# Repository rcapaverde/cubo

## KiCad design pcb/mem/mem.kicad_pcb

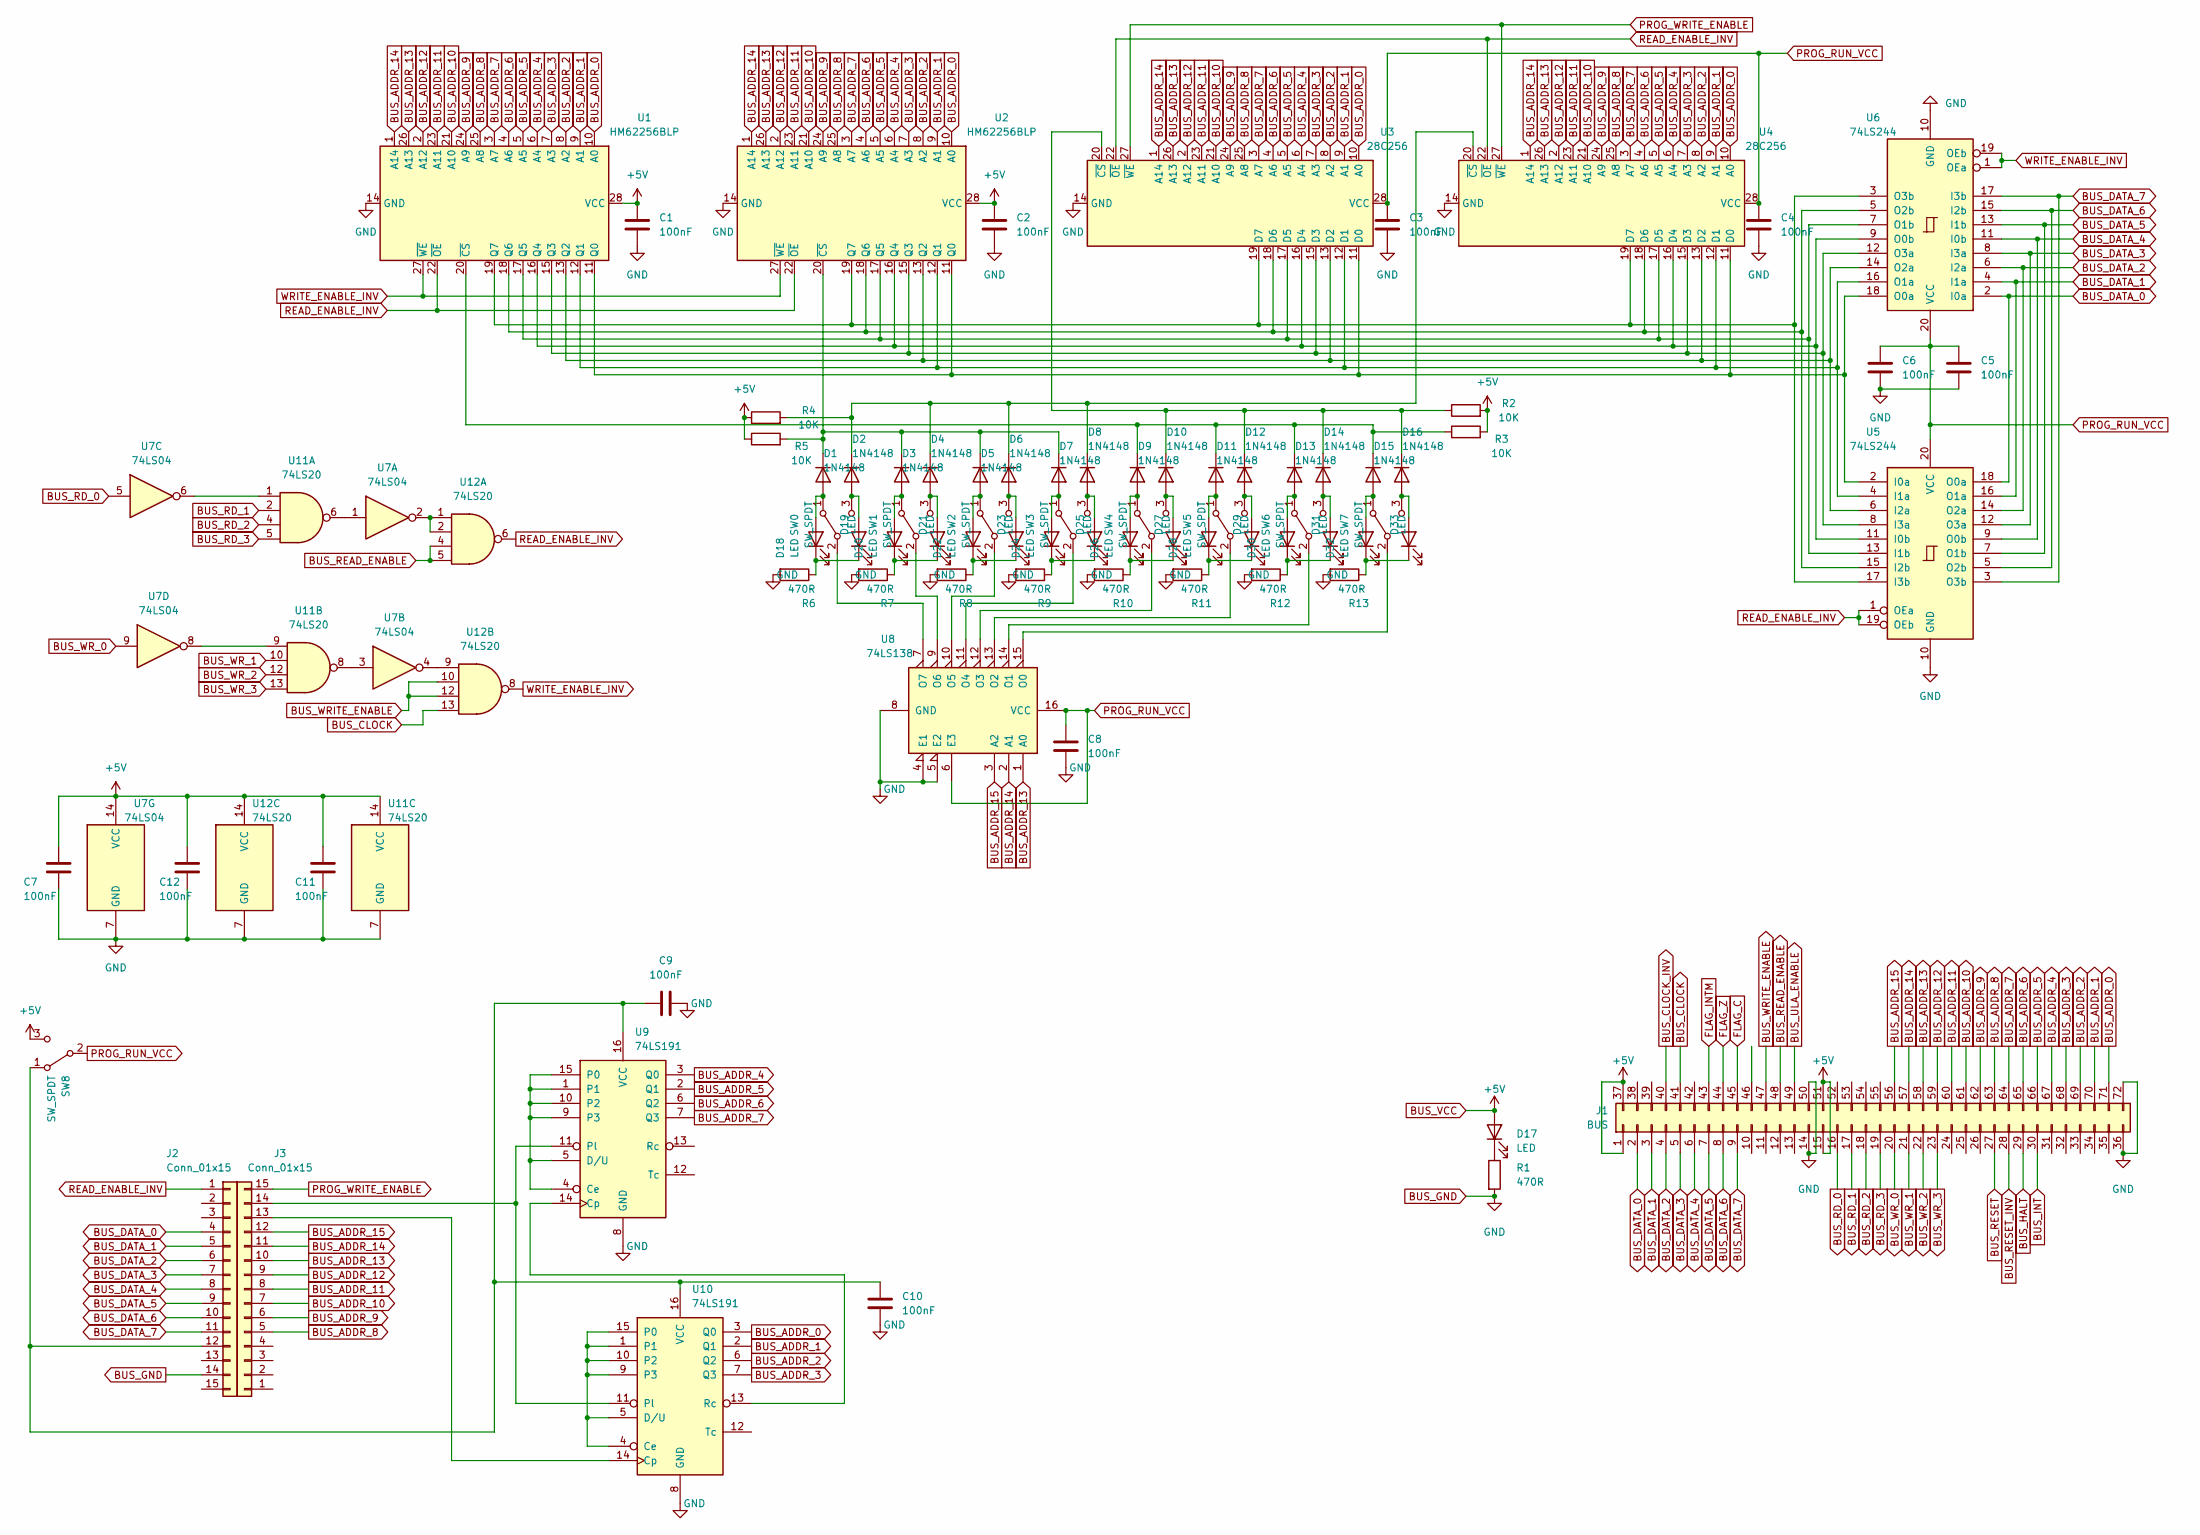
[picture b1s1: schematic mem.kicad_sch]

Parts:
C1, C2, C3, C4, C5, C6, C7, C8, C9, C10, C11, C12: 100nF; C_Disc_D4.3mm_W1.9mm_P5.00mm
D1, D2, D3, D4, D5, D6, D7, D8, D9, D10, D11, D12, D13, D14, D15, D16: 1N4148; D_DO-35_SOD27_P7.62mm_Horizontal
D17, D18, D19, D20, D21, D22, D23, D24, D25, D26, D27, D28, D29, D30, D31, D32, D33: LED; LED_D5.0mm
J1: BUS; Card Edge Slot 28+44
J2, J3: Conn_01x15; PinHeader_1x15_P2.54mm_Vertical
R1, R6, R7, R8, R9, R10, R11, R12, R13: 470R; R_Axial_DIN0204_L3.6mm_D1.6mm_P7.62mm_Horizontal
R2, R3, R4, R5: 10K; R_Axial_DIN0204_L3.6mm_D1.6mm_P7.62mm_Horizontal
SW0, SW1, SW2, SW3, SW4, SW5, SW6, SW7, SW8: SW_SPDT; PinHeader_1x03_P2.54mm_Vertical
U1, U2: HM62256BLP; DIP-28_W15.24mm
U3, U4: 28C256; DIP-28_W15.24mm_Socket
U5, U6: 74LS244; DIP-20_W7.62mm_Socket
U7: 74LS04; DIP-14_W7.62mm_Socket
U8: 74LS138; DIP-16_W7.62mm_Socket
U9, U10: 74LS191; DIP-16_W7.62mm_Socket
U11, U12: 74LS20; DIP-14_W7.62mm_Socket

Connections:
BUS_ADDR_0: J1.71, U1.10 (A0), U2.10 (A0), U3.10 (A0), U4.10 (A0), U10.3 (Q0)
BUS_ADDR_1: J1.70, U1.9 (A1), U2.9 (A1), U3.9 (A1), U4.9 (A1), U10.2 (Q1)
BUS_ADDR_2: J1.69, U1.8 (A2), U2.8 (A2), U3.8 (A2), U4.8 (A2), U10.6 (Q2)
BUS_ADDR_3: J1.68, U1.7 (A3), U2.7 (A3), U3.7 (A3), U4.7 (A3), U10.7 (Q3)
BUS_ADDR_4: J1.67, U1.6 (A4), U2.6 (A4), U3.6 (A4), U4.6 (A4), U9.3 (Q0)
BUS_ADDR_5: J1.66, U1.5 (A5), U2.5 (A5), U3.5 (A5), U4.5 (A5), U9.2 (Q1)
BUS_ADDR_6: J1.65, U1.4 (A6), U2.4 (A6), U3.4 (A6), U4.4 (A6), U9.6 (Q2)
BUS_ADDR_7: J1.64, U1.3 (A7), U2.3 (A7), U3.3 (A7), U4.3 (A7), U9.7 (Q3)
BUS_ADDR_8: J1.63, J3.5, U1.25 (A8), U2.25 (A8), U3.25 (A8), U4.25 (A8)
BUS_ADDR_9: J1.62, J3.6, U1.24 (A9), U2.24 (A9), U3.24 (A9), U4.24 (A9)
BUS_ADDR_10: J1.61, J3.7, U1.21 (A10), U2.21 (A10), U3.21 (A10), U4.21 (A10)
BUS_ADDR_11: J1.60, J3.8, U1.23 (A11), U2.23 (A11), U3.23 (A11), U4.23 (A11)
BUS_ADDR_12: J1.59, J3.9, U1.2 (A12), U2.2 (A12), U3.2 (A12), U4.2 (A12)
BUS_ADDR_13: J1.58, J3.10, U1.26 (A13), U2.26 (A13), U3.26 (A13), U4.26 (A13), U8.1 (A0)
BUS_ADDR_14: J1.57, J3.11, U1.1 (A14), U2.1 (A14), U3.1 (A14), U4.1 (A14), U8.2 (A1)
BUS_ADDR_15: J1.56, J3.12, U8.3 (A2)
BUS_CLOCK: J1.41, U12.13
BUS_CLOCK_INV: J1.40
BUS_DATA_0: J1.2, J2.4, U5.18 (O0a), U6.2 (I0a)
BUS_DATA_1: J1.3, J2.5, U5.16 (O1a), U6.4 (I1a)
BUS_DATA_2: J1.4, J2.6, U5.14 (O2a), U6.6 (I2a)
BUS_DATA_3: J1.5, J2.7, U5.12 (O3a), U6.8 (I3a)
BUS_DATA_4: J1.6, J2.8, U5.9 (O0b), U6.11 (I0b)
BUS_DATA_5: J1.7, J2.9, U5.7 (O1b), U6.13 (I1b)
BUS_DATA_6: J1.8, J2.10, U5.5 (O2b), U6.15 (I2b)
BUS_DATA_7: J1.9, J2.11, U5.3 (O3b), U6.17 (I3b)
BUS_GND: C1.2, C2.2, C3.2, C4.2, C5.2, C6.2, C7.2, C8.2, C9.2, C10.2, C11.2, C12.2, J1.14, J1.36, J1.50, J1.72, J2.14, R1.2, R6.2, R7.2, R8.2, R9.2, R10.2, R11.2, R12.2, R13.2, U1.14 (GND), U2.14 (GND), U3.14 (GND), U4.14 (GND), U5.10 (GND), U6.10 (GND), U7.7 (GND), U8.4 (E1), U8.5 (E2), U8.8 (GND), U9.8 (GND), U10.8 (GND), U11.7 (GND), U12.7 (GND); also elsewhere on the board
BUS_HALT: J1.29
BUS_INT: J1.30
BUS_RD_0: J1.16, U7.5
BUS_RD_1: J1.17, U11.2
BUS_RD_2: J1.18, U11.4
BUS_RD_3: J1.19, U11.5
BUS_RESET: J1.27
BUS_RESET_INV: J1.28
BUS_ULA_ENABLE: J1.49
BUS_VCC: C1.1, C2.1, C7.1, C11.1, C12.1, D17.2 (A), J1.1, J1.15, J1.37, J1.51, R2.2, R3.2, R4.1, R5.1, SW8.3 (C), U1.28 (VCC), U2.28 (VCC), U7.14 (VCC), U11.14 (VCC), U12.14 (VCC)
BUS_WR_0: J1.20, U7.9
BUS_WR_1: J1.21, U11.10
BUS_WR_2: J1.22, U11.12
BUS_WR_3: J1.23, U11.13
FLAG_C: J1.45
FLAG_INTM: J1.43
FLAG_Z: J1.44
unnamed: D1.1 (K), D3.1 (K), D5.1 (K), D7.1 (K), R5.2, U2.20 (~CS)
unnamed: D2.1 (K), D4.1 (K), D6.1 (K), D8.1 (K), R4.2, U4.20 (~CS)
unnamed: D3.2 (A), D20.2 (A), SW1.1 (A)
unnamed: D4.2 (A), D21.2 (A), SW1.3 (C)
unnamed: D5.2 (A), D22.2 (A), SW2.1 (A)
unnamed: D6.2 (A), D23.2 (A), SW2.3 (C)
unnamed: D7.2 (A), D24.2 (A), SW3.1 (A)
unnamed: D8.2 (A), D25.2 (A), SW3.3 (C)
unnamed: D9.2 (A), D26.2 (A), SW4.1 (A)
unnamed: D10.1 (K), D12.1 (K), D14.1 (K), D16.1 (K), R2.1, U3.20 (~CS)
unnamed: D10.2 (A), D27.2 (A), SW4.3 (C)
unnamed: D9.1 (K), D11.1 (K), D13.1 (K), D15.1 (K), R3.1, U1.20 (~CS)
unnamed: D11.2 (A), D28.2 (A), SW5.1 (A)
unnamed: D12.2 (A), D29.2 (A), SW5.3 (C)
unnamed: D13.2 (A), D30.2 (A), SW6.1 (A)
unnamed: D14.2 (A), D31.2 (A), SW6.3 (C)
unnamed: D15.2 (A), D32.2 (A), SW7.1 (A)
unnamed: D16.2 (A), D33.2 (A), SW7.3 (C)
unnamed: D17.1 (K), R1.1
unnamed 63: D18.1 (K), D19.1 (K), R6.1; also elsewhere on the board
unnamed: D20.1 (K), D21.1 (K), R7.1
unnamed: D22.1 (K), D23.1 (K), R8.1
unnamed: D24.1 (K), D25.1 (K), R9.1
unnamed: D26.1 (K), D27.1 (K), R10.1
unnamed: D28.1 (K), D29.1 (K), R11.1
unnamed: D30.1 (K), D31.1 (K), R12.1
unnamed: D32.1 (K), D33.1 (K), R13.1
unnamed: SW0.2 (B), U8.7 (O7)
unnamed: SW1.2 (B), U8.9 (O6)
unnamed: SW2.2 (B), U8.10 (O5)
unnamed: SW3.2 (B), U8.11 (O4)
unnamed: SW4.2 (B), U8.12 (O3)
unnamed: SW5.2 (B), U8.13 (O2)
unnamed: SW6.2 (B), U8.14 (O1)
unnamed: SW7.2 (B), U8.15 (O0)
unnamed: C9.1, C10.1, J2.12, SW8.1 (A), U9.16 (VCC), U10.16 (VCC)
unnamed: U1.11 (Q0), U2.11 (Q0), U3.11 (D0), U4.11 (D0), U5.2 (I0a), U6.18 (O0a)
unnamed: U1.12 (Q1), U2.12 (Q1), U3.12 (D1), U4.12 (D1), U5.4 (I1a), U6.16 (O1a)
unnamed: U1.13 (Q2), U2.13 (Q2), U3.13 (D2), U4.13 (D2), U5.6 (I2a), U6.14 (O2a)
unnamed: U1.15 (Q3), U2.15 (Q3), U3.15 (D3), U4.15 (D3), U5.8 (I3a), U6.12 (O3a)
unnamed: U1.16 (Q4), U2.16 (Q4), U3.16 (D4), U4.16 (D4), U5.11 (I0b), U6.9 (O0b)
unnamed: U1.17 (Q5), U2.17 (Q5), U3.17 (D5), U4.17 (D5), U5.13 (I1b), U6.7 (O1b)
unnamed: U1.18 (Q6), U2.18 (Q6), U3.18 (D6), U4.18 (D6), U5.15 (I2b), U6.5 (O2b)
unnamed: U1.19 (Q7), U2.19 (Q7), U3.19 (D7), U4.19 (D7), U5.17 (I3b), U6.3 (O3b)
unnamed: U7.2, U12.1, U12.2
unnamed: U7.4, U12.9
unnamed: U7.6, U11.1
unnamed: U9.1, U9.4 (Ce), U9.5 (D/U), U9.9 (P3), U9.10 (P2), U9.15 (P0)
unnamed: J3.14, U9.11 (Pl), U10.11 (Pl)
unnamed: U9.14 (Cp), U10.13 (Rc)
unnamed: J3.13, U10.14 (Cp)
unnamed: U10.1, U10.4 (Ce), U10.5 (D/U), U10.9 (P3), U10.10 (P2), U10.15 (P0)
unnamed: U7.1, U11.6
unnamed: U7.3, U11.8
unnamed: U7.8, U11.9
PROG_RUN_VCC: C3.1, C4.1, C5.1, C6.1, C8.1, SW8.2 (B), U3.28 (VCC), U4.28 (VCC), U5.20 (VCC), U6.20 (VCC), U8.6 (E3), U8.16 (VCC)
PROG_WRITE_ENABLE: J3.15, U3.27 (~WE), U4.27 (~WE)
READ_ENABLE_INV: J2.1, U1.22 (~OE), U2.22 (~OE), U3.22 (~OE), U4.22 (~OE), U5.1 (OEa), U5.19 (OEb), U12.6
WRITE_ENABLE_INV: U1.27 (~WE), U2.27 (~WE), U6.1 (OEa), U6.19 (OEb), U12.8

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
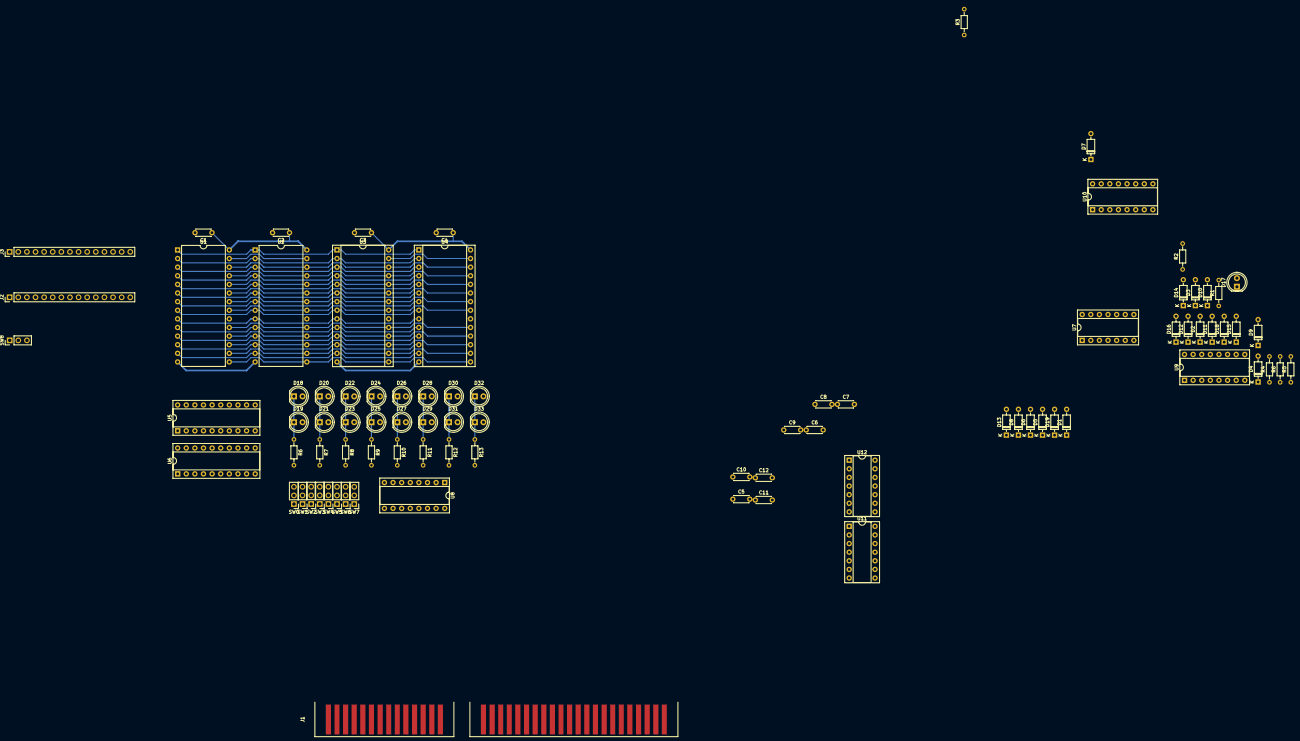
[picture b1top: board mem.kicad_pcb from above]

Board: 2 copper layers, 85 parts (0 on the bottom side), 98 nets.

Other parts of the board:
D18#2, D19#2: LED; LED_D5.0mm
R6#2: 10K; R_Axial_DIN0204_L3.6mm_D1.6mm_P7.62mm_Horizontal

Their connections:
BUS_GND: R6#2.1; also elsewhere on the board
unnamed 63: D18#2.1 (K), D19#2.1 (K), R6#2.2; also elsewhere on the board

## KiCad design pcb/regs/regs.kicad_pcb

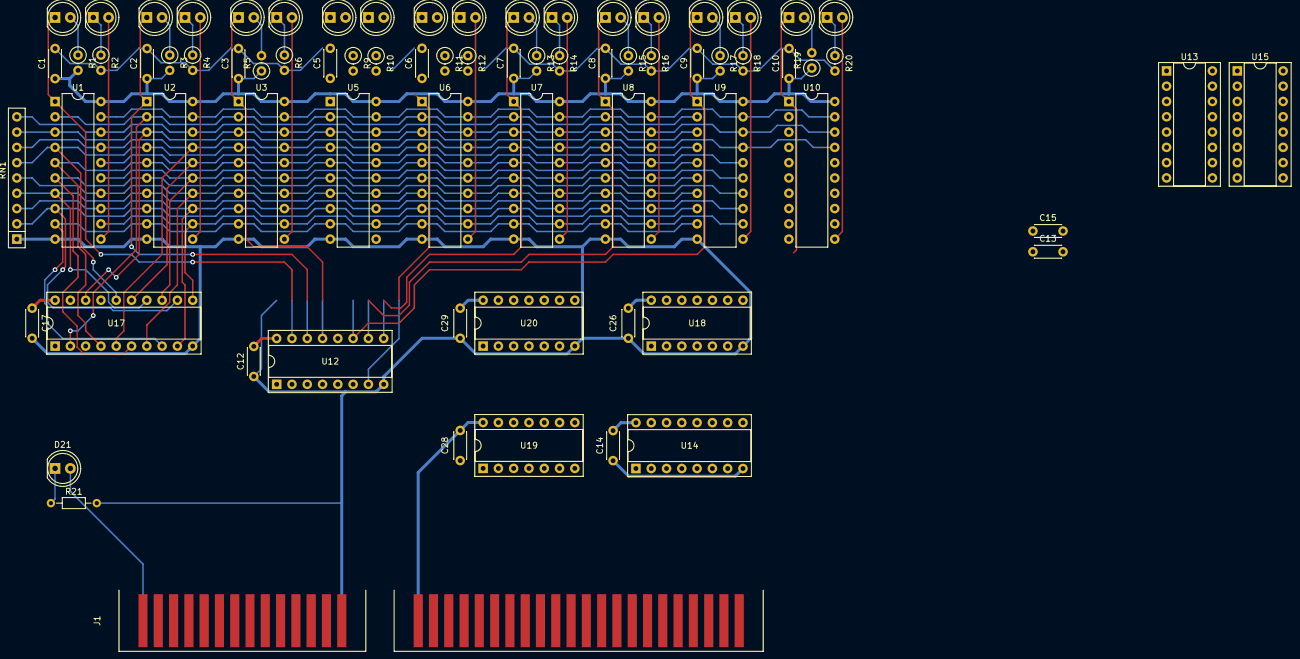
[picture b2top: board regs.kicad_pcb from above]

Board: 2 copper layers, 74 parts (0 on the bottom side), 78 nets.

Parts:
C1, C2, C3, C5, C6, C7, C8, C9, C10, C12, C13, C14, C15, C17, C26, C28, C29: 100nF; C_Disc_D4.3mm_W1.9mm_P5.00mm
D1, D2, D3, D4, D5, D6, D9, D10, D11, D12, D13, D14, D15, D16, D17, D18, D19, D20, D21: LED; LED_D5.0mm
J1: BUS; Card Edge Slot 28+44
R1, R2, R3, R4, R5, R6, R9, R10, R11, R12, R13, R14, R15, R16, R17, R18, R19, R20: 470R; R_Axial_DIN0207_L6.3mm_D2.5mm_P2.54mm_Vertical
R21: 470R; R_Axial_DIN0204_L3.6mm_D1.6mm_P7.62mm_Horizontal
RN1: 4K7; R_Array_SIP9
U1, U2, U3, U5, U6, U7, U8, U9, U10: 74LS374; DIP-20_W7.62mm
U12, U13, U14, U15: 74LS138; DIP-16_W7.62mm_Socket
U17: 74LS244; DIP-20_W7.62mm_Socket
U18: 74LS00; DIP-14_W7.62mm_Socket
U19, U20: 74LS06; DIP-14_W7.62mm_Socket

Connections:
BUS_CLOCK: J1.41, U18.2
BUS_DATA_0: J1.2, U1.2 (O0), U2.2 (O0), U3.2 (O0), U5.2 (O0), U6.2 (O0), U7.2 (O0), U8.2 (O0), U9.2 (O0), U10.2 (O0), U17.2 (I0a)
BUS_DATA_1: J1.3, U1.5 (O1), U2.5 (O1), U3.5 (O1), U5.5 (O1), U6.5 (O1), U7.5 (O1), U8.5 (O1), U9.5 (O1), U10.5 (O1), U17.4 (I1a)
BUS_DATA_2: J1.4, U1.6 (O2), U2.6 (O2), U3.6 (O2), U5.6 (O2), U6.6 (O2), U7.6 (O2), U8.6 (O2), U9.6 (O2), U10.6 (O2), U17.6 (I2a)
BUS_DATA_3: J1.5, U1.9 (O3), U2.9 (O3), U3.9 (O3), U5.9 (O3), U6.9 (O3), U7.9 (O3), U8.9 (O3), U9.9 (O3), U10.9 (O3), U17.8 (I3a)
BUS_DATA_4: J1.6, U1.12 (O4), U2.12 (O4), U3.12 (O4), U5.12 (O4), U6.12 (O4), U7.12 (O4), U8.12 (O4), U9.12 (O4), U10.12 (O4), U17.11 (I0b)
BUS_DATA_5: J1.7, U1.15 (O5), U2.15 (O5), U3.15 (O5), U5.15 (O5), U6.15 (O5), U7.15 (O5), U8.15 (O5), U9.15 (O5), U10.15 (O5), U17.13 (I1b)
BUS_DATA_6: J1.8, U1.16 (O6), U2.16 (O6), U3.16 (O6), U5.16 (O6), U6.16 (O6), U7.16 (O6), U8.16 (O6), U9.16 (O6), U10.16 (O6), U17.15 (I2b)
BUS_DATA_7: J1.9, U1.19 (O7), U2.19 (O7), U3.19 (O7), U5.19 (O7), U6.19 (O7), U7.19 (O7), U8.19 (O7), U9.19 (O7), U10.19 (O7), U17.17 (I3b)
BUS_GND: C1.2, C2.2, C3.2, C5.2, C6.2, C7.2, C8.2, C9.2, C10.2, C12.1, C13.1, C14.1, C15.1, C17.2, C26.2, C28.2, C29.2, J1.14, J1.36, J1.50, J1.72, R2.2, R4.2, R6.2, R10.2, R12.2, R14.2, R16.2, R18.2, R20.2, R21.2, RN1.1 (R1.1), U1.10 (GND), U2.10 (GND), U3.10 (GND), U5.10 (GND), U6.10 (GND), U7.10 (GND), U8.10 (GND), U9.10 (GND), U10.10 (GND), U12.8 (GND), U13.8 (GND), U14.8 (GND), U15.8 (GND), U17.10 (GND), U18.7 (GND), U19.7 (GND), U20.7 (GND)
BUS_RD_0: J1.16, U12.1 (A0), U13.1 (A0)
BUS_RD_1: J1.17, U12.2 (A1), U13.2 (A1)
BUS_RD_2: J1.18, U12.3 (A2), U13.3 (A2)
BUS_RD_3: J1.19, U12.6 (E3), U13.4 (E1), U13.5 (E2)
BUS_READ_ENABLE: J1.48, U13.6 (E3), U18.4, U18.5
BUS_VCC: C1.1, C2.1, C3.1, C5.1, C6.1, C7.1, C8.1, C9.1, C10.1, C12.2, C13.2, C14.2, C15.2, C17.1, C26.1, C28.1, C29.1, D21.2 (A), J1.1, J1.15, J1.37, J1.51, R1.2, R3.2, R5.1, R9.1, R11.1, R13.2, R15.2, R17.2, R19.1, U1.20 (VCC), U2.20 (VCC), U3.20 (VCC), U5.20 (VCC), U6.20 (VCC), U7.20 (VCC), U8.20 (VCC), U9.20 (VCC), U10.20 (VCC), U12.16 (VCC), U13.16 (VCC), U14.16 (VCC), U15.16 (VCC), U17.20 (VCC), U18.14 (VCC), U19.14 (VCC), U20.14 (VCC)
BUS_WRITE_ENABLE: J1.47, U17.1 (OEa), U17.19 (OEb), U18.1
BUS_WR_0: J1.20, U14.1 (A0), U15.1 (A0)
BUS_WR_1: J1.21, U14.2 (A1), U15.2 (A1)
BUS_WR_2: J1.22, U14.3 (A2), U15.3 (A2)
BUS_WR_3: J1.23, U14.6 (E3), U15.4 (E1), U15.5 (E2)
DATA_0: RN1.8 (R7.2), U1.3 (D0), U2.3 (D0), U3.3 (D0), U5.3 (D0), U6.3 (D0), U7.3 (D0), U8.3 (D0), U9.3 (D0), U10.3 (D0), U17.18 (O0a)
DATA_1: RN1.6 (R5.2), U1.4 (D1), U2.4 (D1), U3.4 (D1), U5.4 (D1), U6.4 (D1), U7.4 (D1), U8.4 (D1), U9.4 (D1), U10.4 (D1), U17.16 (O1a)
DATA_2: RN1.4 (R3.2), U1.7 (D2), U2.7 (D2), U3.7 (D2), U5.7 (D2), U6.7 (D2), U7.7 (D2), U8.7 (D2), U9.7 (D2), U10.7 (D2), U17.14 (O2a)
DATA_3: RN1.2 (R1.2), U1.8 (D3), U2.8 (D3), U3.8 (D3), U5.8 (D3), U6.8 (D3), U7.8 (D3), U8.8 (D3), U9.8 (D3), U10.8 (D3), U17.12 (O3a)
DATA_4: RN1.3 (R2.2), U1.13 (D4), U2.13 (D4), U3.13 (D4), U5.13 (D4), U6.13 (D4), U7.13 (D4), U8.13 (D4), U9.13 (D4), U10.13 (D4), U17.9 (O0b)
DATA_5: RN1.5 (R4.2), U1.14 (D5), U2.14 (D5), U3.14 (D5), U5.14 (D5), U6.14 (D5), U7.14 (D5), U8.14 (D5), U9.14 (D5), U10.14 (D5), U17.7 (O1b)
DATA_6: RN1.7 (R6.2), U1.17 (D6), U2.17 (D6), U3.17 (D6), U5.17 (D6), U6.17 (D6), U7.17 (D6), U8.17 (D6), U9.17 (D6), U10.17 (D6), U17.5 (O2b)
DATA_7: RN1.9 (R8.2), U1.18 (D7), U2.18 (D7), U3.18 (D7), U5.18 (D7), U6.18 (D7), U7.18 (D7), U8.18 (D7), U9.18 (D7), U10.18 (D7), U17.3 (O3b)
unnamed: D1.2 (A), R1.1
unnamed: D2.1 (K), R2.1
unnamed: D3.2 (A), R3.1
unnamed: D4.1 (K), R4.1
unnamed: D5.2 (A), R5.2
unnamed: D6.1 (K), R6.1
unnamed: D9.2 (A), R9.2
unnamed: D10.1 (K), R10.1
unnamed: D11.2 (A), R11.2
unnamed: D12.1 (K), R12.1
unnamed: D13.2 (A), R13.1
unnamed: D14.1 (K), R14.1
unnamed: D15.2 (A), R15.1
unnamed: D16.1 (K), R16.1
unnamed: D17.2 (A), R17.1
unnamed: D18.1 (K), R18.1
unnamed: D19.2 (A), R19.2
unnamed: D20.1 (K), R20.1
unnamed: D21.1 (K), R21.1
unnamed: U12.4 (E1), U12.5 (E2), U18.6
unnamed: U14.4 (E1), U14.5 (E2), U18.3, U18.9, U18.10
unnamed: U14.7 (O7), U20.9
unnamed: U14.9 (O6), U20.5
unnamed: U14.10 (O5), U20.3
unnamed: U14.11 (O4), U20.1
unnamed: U14.13 (O2), U19.5
unnamed: U14.14 (O1), U19.3
unnamed: U14.15 (O0), U19.1
unnamed: U15.6 (E3), U18.8
unnamed: U15.9 (O6), U19.9
unnamed: U15.7 (O7), U19.11
RD_A_INV: D1.1 (K), U1.1 (OE), U12.15 (O0)
RD_B_INV: D3.1 (K), U2.1 (OE), U12.14 (O1)
RD_C_INV: D5.1 (K), U3.1 (OE), U12.13 (O2)
RD_SPH_INV: D17.1 (K), U9.1 (OE), U13.7 (O7)
RD_SPL_INV: D19.1 (K), U10.1 (OE), U13.9 (O6)
RD_XH_INV: D15.1 (K), U8.1 (OE), U12.10 (O5)
RD_XL_INV: D13.1 (K), U7.1 (OE), U12.11 (O4)
RD_YH_INV: D11.1 (K), U6.1 (OE), U12.7 (O7)
RD_YL_INV: D9.1 (K), U5.1 (OE), U12.9 (O6)
WR_A: D2.2 (A), U1.11 (Cp), U19.2
WR_B: D4.2 (A), U2.11 (Cp), U19.4
WR_C: D6.2 (A), U3.11 (Cp), U19.6
WR_SPH: D18.2 (A), U9.11 (Cp), U19.10
WR_SPL: D20.2 (A), U10.11 (Cp), U19.8
WR_XH: D16.2 (A), U8.11 (Cp), U20.4
WR_XL: D14.2 (A), U7.11 (Cp), U20.2
WR_YH: D12.2 (A), U6.11 (Cp), U20.8
WR_YL: D10.2 (A), U5.11 (Cp), U20.6

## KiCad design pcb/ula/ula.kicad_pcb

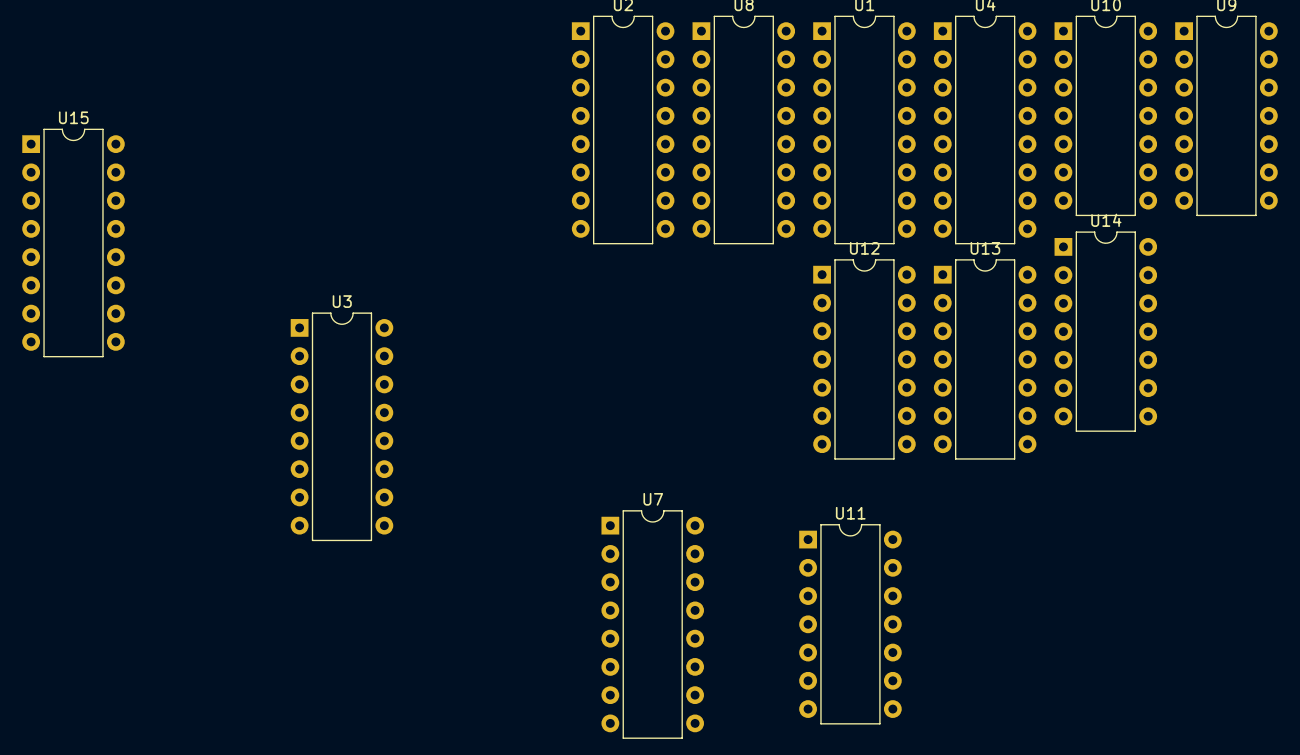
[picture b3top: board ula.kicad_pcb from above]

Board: 2 copper layers, 13 parts (0 on the bottom side), 22 nets, no tracks yet.

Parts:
U1, U2, U3, U4: 74LS283; DIP-16_W7.62mm
U7, U8, U15: 74LS175; DIP-16_W7.62mm
U9, U10: 74LS08; DIP-14_W7.62mm
U11, U12: 74LS32; DIP-14_W7.62mm
U13, U14: 74LS86; DIP-14_W7.62mm

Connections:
+5V: U1.16 (VCC), U2.16 (VCC), U3.16 (VCC), U4.16 (VCC), U7.16 (VCC), U8.16 (VCC), U9.14 (VCC), U10.14 (VCC), U11.14 (VCC), U12.14 (VCC), U13.14 (VCC), U14.14 (VCC), U15.16 (VCC)
FLAG_C: U1.7 (C0), U15.7 (Q1)
FLAG_C_INV: U3.7 (C0), U15.6 (~Q1)
GND: U1.8 (GND), U2.8 (GND), U3.8 (GND), U4.8 (GND), U7.8 (GND), U8.8 (GND), U9.7 (GND), U10.7 (GND), U11.7 (GND), U12.7 (GND), U13.7 (GND), U14.7 (GND), U15.8 (GND)
unnamed: U1.9 (C4), U2.7 (C0)
unnamed: U2.2 (B2), U8.7 (Q1), U10.5, U12.5, U14.5
unnamed: U2.15 (B3), U8.10 (Q2), U10.10, U12.10, U14.10
unnamed: U3.9 (C4), U4.7 (C0)
unnamed: U1.6 (B1), U7.2 (Q0), U9.2, U11.2, U13.2
unnamed: U3.6 (B1), U7.3 (~Q0)
unnamed: U3.2 (B2), U7.6 (~Q1)
unnamed: U1.2 (B2), U7.7 (Q1), U9.5, U11.5, U13.5
unnamed: U1.15 (B3), U7.10 (Q2), U9.10, U11.10, U13.10
unnamed: U3.15 (B3), U7.11 (~Q2)
unnamed: U3.11 (B4), U7.14 (~Q3)
unnamed: U1.11 (B4), U7.15 (Q3), U9.13, U11.13, U13.13
unnamed: U4.6 (B1), U8.3 (~Q0)
unnamed: U4.2 (B2), U8.6 (~Q1)
unnamed: U4.15 (B3), U8.11 (~Q2)
unnamed: U4.11 (B4), U8.14 (~Q3)
unnamed: U2.11 (B4), U8.15 (Q3), U10.13, U12.13, U14.13
unnamed: U2.6 (B1), U8.2 (Q0), U10.2, U12.2, U14.2

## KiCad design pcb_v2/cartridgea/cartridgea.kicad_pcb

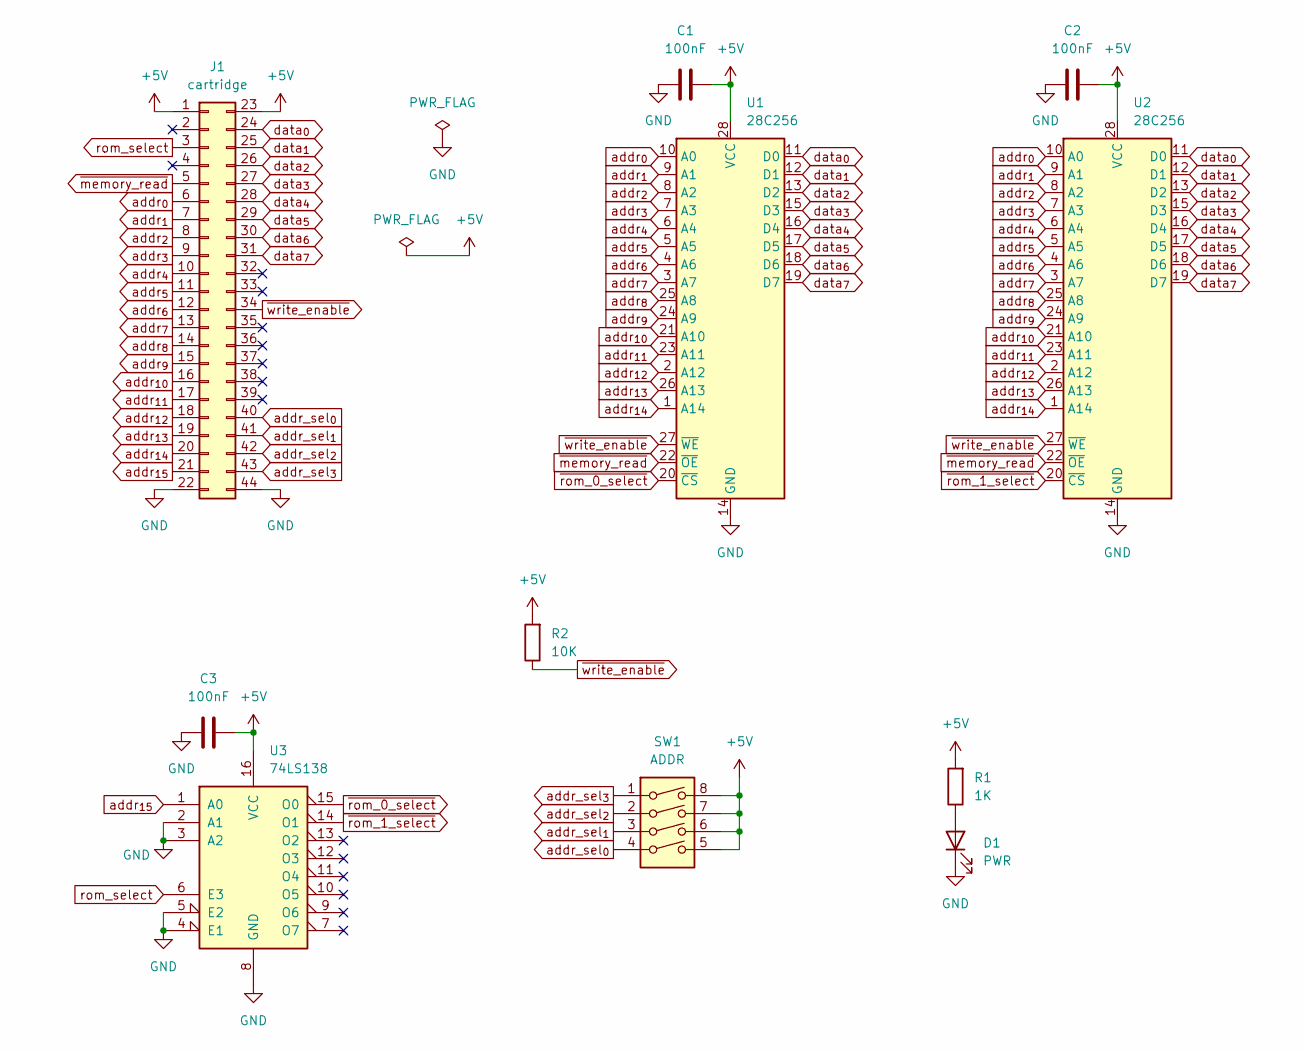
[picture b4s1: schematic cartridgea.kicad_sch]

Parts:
C1, C2, C3: 100nF; C_Disc_D5.1mm_W3.2mm_P5.00mm
D1: PWR; LED_D5.0mm
J1: cartridge; edge-connector-44
R1: 1K; R_Axial_DIN0207_L6.3mm_D2.5mm_P7.62mm_Horizontal
R2: 10K; R_Axial_DIN0207_L6.3mm_D2.5mm_P7.62mm_Horizontal
SW1: ADDR; DIP-8_W7.62mm
U1, U2: 28C256; DIP-28_W15.24mm
U3: 74LS138; DIP-16_W7.62mm

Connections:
+5V: C1.2, C2.2, C3.2, J1.1, J1.23, R1.2, R2.2, SW1.5, SW1.6, SW1.7, SW1.8, U1.28 (VCC), U2.28 (VCC), U3.16 (VCC)
GND: C1.1, C2.1, C3.1, D1.1 (K), J1.22, J1.44, U1.14 (GND), U2.14 (GND), U3.2 (A1), U3.3 (A2), U3.4 (E1), U3.5 (E2), U3.8 (GND)
unnamed: D1.2 (A), R1.1
addr_sel_{0}: J1.40, SW1.4
addr_sel_{1}: J1.41, SW1.3
addr_sel_{2}: J1.42, SW1.2
addr_sel_{3}: J1.43, SW1.1
addr_{0}: J1.6, U1.10 (A0), U2.10 (A0)
addr_{1}: J1.7, U1.9 (A1), U2.9 (A1)
addr_{2}: J1.8, U1.8 (A2), U2.8 (A2)
addr_{3}: J1.9, U1.7 (A3), U2.7 (A3)
addr_{4}: J1.10, U1.6 (A4), U2.6 (A4)
addr_{5}: J1.11, U1.5 (A5), U2.5 (A5)
addr_{6}: J1.12, U1.4 (A6), U2.4 (A6)
addr_{7}: J1.13, U1.3 (A7), U2.3 (A7)
addr_{8}: J1.14, U1.25 (A8), U2.25 (A8)
addr_{9}: J1.15, U1.24 (A9), U2.24 (A9)
addr_{10}: J1.16, U1.21 (A10), U2.21 (A10)
addr_{11}: J1.17, U1.23 (A11), U2.23 (A11)
addr_{12}: J1.18, U1.2 (A12), U2.2 (A12)
addr_{13}: J1.19, U1.26 (A13), U2.26 (A13)
addr_{14}: J1.20, U1.1 (A14), U2.1 (A14)
addr_{15}: J1.21, U3.1 (A0)
data_{0}: J1.24, U1.11 (D0), U2.11 (D0)
data_{1}: J1.25, U1.12 (D1), U2.12 (D1)
data_{2}: J1.26, U1.13 (D2), U2.13 (D2)
data_{3}: J1.27, U1.15 (D3), U2.15 (D3)
data_{4}: J1.28, U1.16 (D4), U2.16 (D4)
data_{5}: J1.29, U1.17 (D5), U2.17 (D5)
data_{6}: J1.30, U1.18 (D6), U2.18 (D6)
data_{7}: J1.31, U1.19 (D7), U2.19 (D7)
rom_select: J1.3, U3.6 (E3)
~memory_read: J1.5, U1.22 (~OE), U2.22 (~OE)
~rom_0_select: U1.20 (~CS), U3.15 (O0)
~rom_1_select: U2.20 (~CS), U3.14 (O1)
~write_enable: J1.34, R2.1, U1.27 (~WE), U2.27 (~WE)

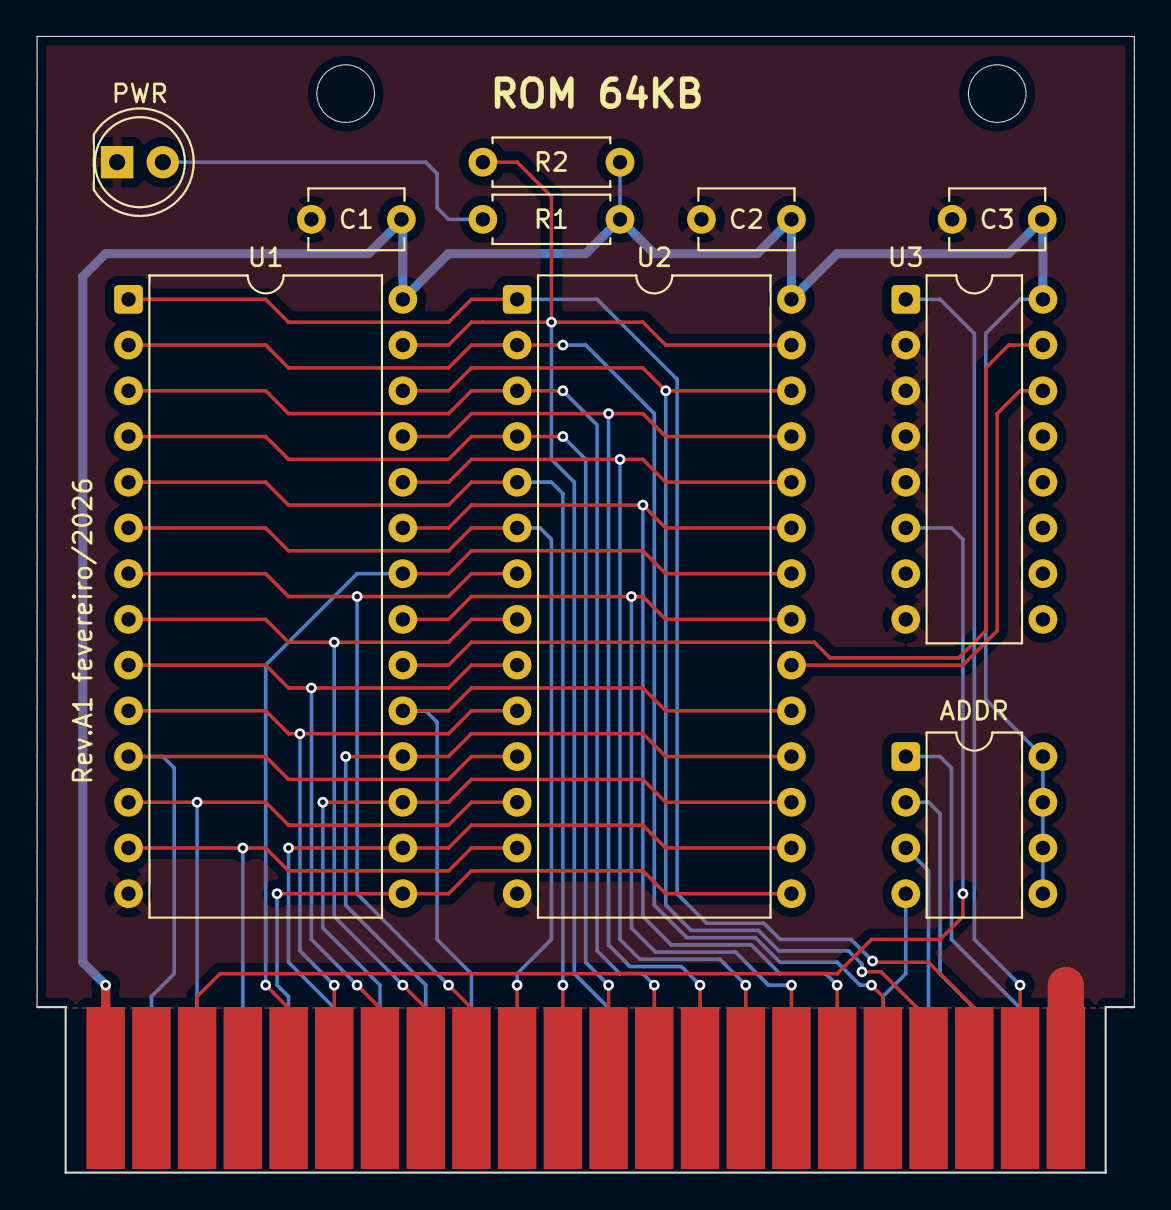
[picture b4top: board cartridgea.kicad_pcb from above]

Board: 2 copper layers, 61.0 x 63.1 mm, 11 parts (0 on the bottom side), 36 nets.

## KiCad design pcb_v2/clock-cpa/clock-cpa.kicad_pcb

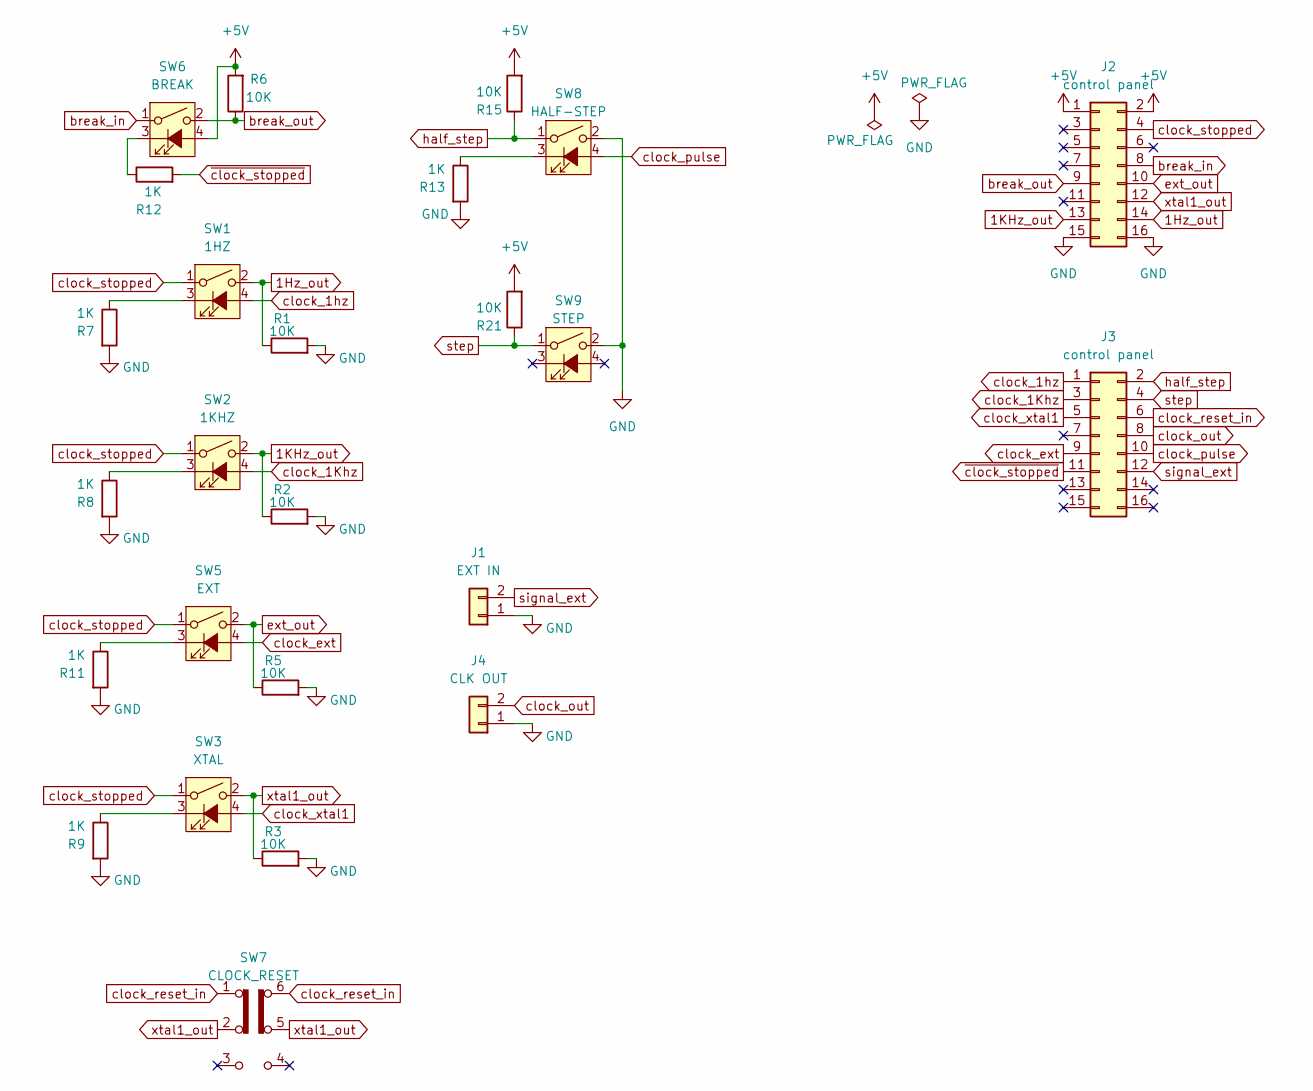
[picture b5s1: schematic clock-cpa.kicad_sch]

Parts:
J1: EXT IN; JST_XH_B2B-XH-A_1x02_P2.50mm_Vertical
J2, J3: control panel; PinHeader_2x08_P2.54mm_Vertical
J4: CLK OUT; JST_XH_B2B-XH-A_1x02_P2.50mm_Vertical
R1, R2, R3, R5, R6, R15, R21: 10K; R_Axial_DIN0207_L6.3mm_D2.5mm_P7.62mm_Horizontal
R7, R8, R9, R11, R12, R13: 1K; R_Axial_DIN0207_L6.3mm_D2.5mm_P7.62mm_Horizontal
SW1: 1HZ; TS5 LED Momentary Click Tact Switch
SW2: 1KHZ; TS5 LED Momentary Click Tact Switch
SW3: XTAL; TS5 LED Momentary Click Tact Switch
SW5: EXT; TS5 LED Momentary Click Tact Switch
SW6: BREAK; TS5 LED Momentary Click Tact Switch
SW7: CLOCK_RESET; Slide Switch DPDT
SW8: HALF-STEP; TS5 LED Momentary Click Tact Switch
SW9: STEP; TS5 LED Momentary Click Tact Switch

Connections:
1Hz_out: J2.14, R1.1, SW1.2
1KHz_out: J2.13, R2.1, SW2.2
+5V: J2.1, J2.2, R6.2, R15.2, R21.2, SW6.4 (A)
GND: J1.1, J2.15, J2.16, J4.1, R1.2, R2.2, R3.2, R5.2, R7.2, R8.2, R9.2, R11.2, R13.2, SW8.2, SW9.2
unnamed: R7.1, SW1.3 (K)
unnamed: R8.1, SW2.3 (K)
unnamed: R9.1, SW3.3 (K)
unnamed: R11.1, SW5.3 (K)
unnamed: R12.1, SW6.3 (K)
unnamed: R13.1, SW8.3 (K)
break_in: J2.8, SW6.1
break_out: J2.9, R6.1, SW6.2
clock_1Khz: J3.3, SW2.4 (A)
clock_1hz: J3.1, SW1.4 (A)
clock_ext: J3.9, SW5.4 (A)
clock_out: J3.8, J4.2
clock_pulse: J3.10, SW8.4 (A)
clock_reset_in: J3.6, SW7.1 (A), SW7.6 (C)
clock_stopped: J2.4, SW1.1, SW2.1, SW3.1, SW5.1
clock_xtal1: J3.5, SW3.4 (A)
ext_out: J2.10, R5.1, SW5.2
half_step: J3.2, R15.1, SW8.1
signal_ext: J1.2, J3.12
step: J3.4, R21.1, SW9.1
xtal1_out: J2.12, R3.1, SW3.2, SW7.2 (B), SW7.5 (B)
~clock_stopped: J3.11, R12.2

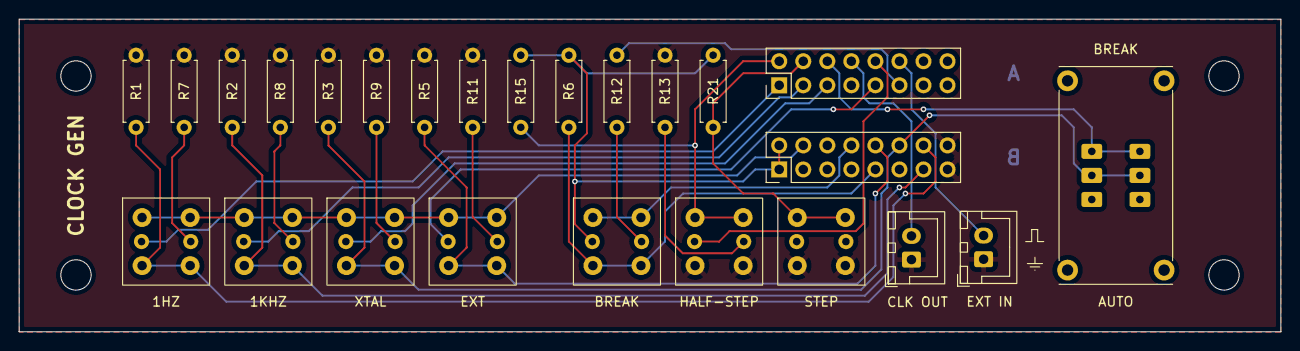
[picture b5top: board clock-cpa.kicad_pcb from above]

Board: 2 copper layers, 133.3 x 33.0 mm, 25 parts (0 on the bottom side), 26 nets.
